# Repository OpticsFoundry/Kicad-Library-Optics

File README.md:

# KiCad Library for Optics

This repository includes a library for designing optical setups in KiCad.

Please visit our [website](https://www.opticsfoundry.com/) for more product and ordering.  
If you have any question or need help, write to us: opticsfoundry@gmail.com

## Table of Contents
- [Introduction](#introduction)
- [How to add library to KiCad](#how-to-add-library-to-kiCad)
- [Start a new design](#start-a-new-design)
  - [Schematic](#schematic)
  - [PCB](#pcb)
- [Free Projects](#free-projects)

---

## Introduction

[KiCad](https://www.kicad.org/) is an open source electronic design software. However, we have developed this library to be able to design optical setup.
The procedure of producing an optical setup with Robot developed by OpticsFoundry is shown below.

## How to add library to KiCad

1. Install KiCad from [here](https://www.kicad.org/),
2. Download or clone this repository to your computer as shown below,

3. Unzip the downloaded folder and move the folder to an appropriate path if you want,
4. Open the KiCad software, from `Preferences` tab, click on `Configure Paths...` as shown below,

5. Add a new path, name it `KIGITHUB` with path `https://github.com/KiCad`. As shown below,

6. Add another one and name it `KICAD_FIREFLY_OPTICS`, for the path click on folder icon and go to the path which the library has been downloaded then select `Optics` folder. As shown in following pictures,

7. At the end click on `OK` and close the window,
8. Now from `Preferences` tab, click on `Manage Symbol Libraries...`,
9. Add a new row and call it `Optics` with library path `${KICAD_FIREFLY_OPTICS}/Symbols/Optics.kicad_sym`. As shown below,

10. Then click on `OK` and close the window. If you encounter an error like below, probably the path is not defined correctly,

11. From `Preferences` tab, click on `Manage Footprint Libraries...`,
12. Add a new row and call it `Optics` with library path `${KICAD_FIREFLY_OPTICS}/Footprints/Optics.pretty`, at the end click on `OK` and close the window. As shown below,

13. To make sure the library has been added correctly, click on `Symbol Editor` and `Footprint Editor` in `Tools` tab. As shown below,

14. Search for `Optics` library in search bar, you should be able to see list of all the optical symbols and footprint. As shown in following pictures,

15. Done! Now you are ready to start a new optical design.

## Start a new design

Now you can start a new project and open schematic editor to design your optical setup, as shown below.

You could also copy one of the [examples](https://github.com/opticsfoundry/Kicad-Library-Optics/tree/main/Examples/) or use one of the [Free Projects](#free-projects) for starting point.

`Note` Standard optics hight is 7.5 mm, if optics hight of your components is smaller or bigger, please write to us: opticsfoundry@gmail.com

`Note` If you need a specific baseplate size or any other components which are not available in `Symbols`, please write to us: opticsfoundry@gmail.com

### Schematic

Based on your design, you need to choose baseplate size for your board.

If your page size is smaller than baseplate, you can change it in the page settings from `File` tab for schematic and footprint editors.

Schematic editor looks like this after adding baseplate.

I have added two collimators and mirrors to design a fiber to fiber setup.

By selecting wire, you can draw the beam path.

Each component need to be defined by selecting the component and changing the value based on what is your need.

### PCB

After finishing your design, save all changes in schematic editor. NOw you could move to PCB editor and update your PCB from Schematic.

`Note` You could also update PCB design each time after adding any new components.

Click on `Update PCB from Schematic...` in PCB editor, then update PCB and close the window as shown below.

Now the PCB looks like this:

Each component need to be selected and reposition and rerotate based on reality.

This example is available in [test](https://github.com/opticsfoundry/Kicad-Library-Optics/tree/main/Examples/test/)

## Free Projects
1. [AQuRA](https://github.com/opticsfoundry/AQuRA-KiCad-Design-GitHub/)

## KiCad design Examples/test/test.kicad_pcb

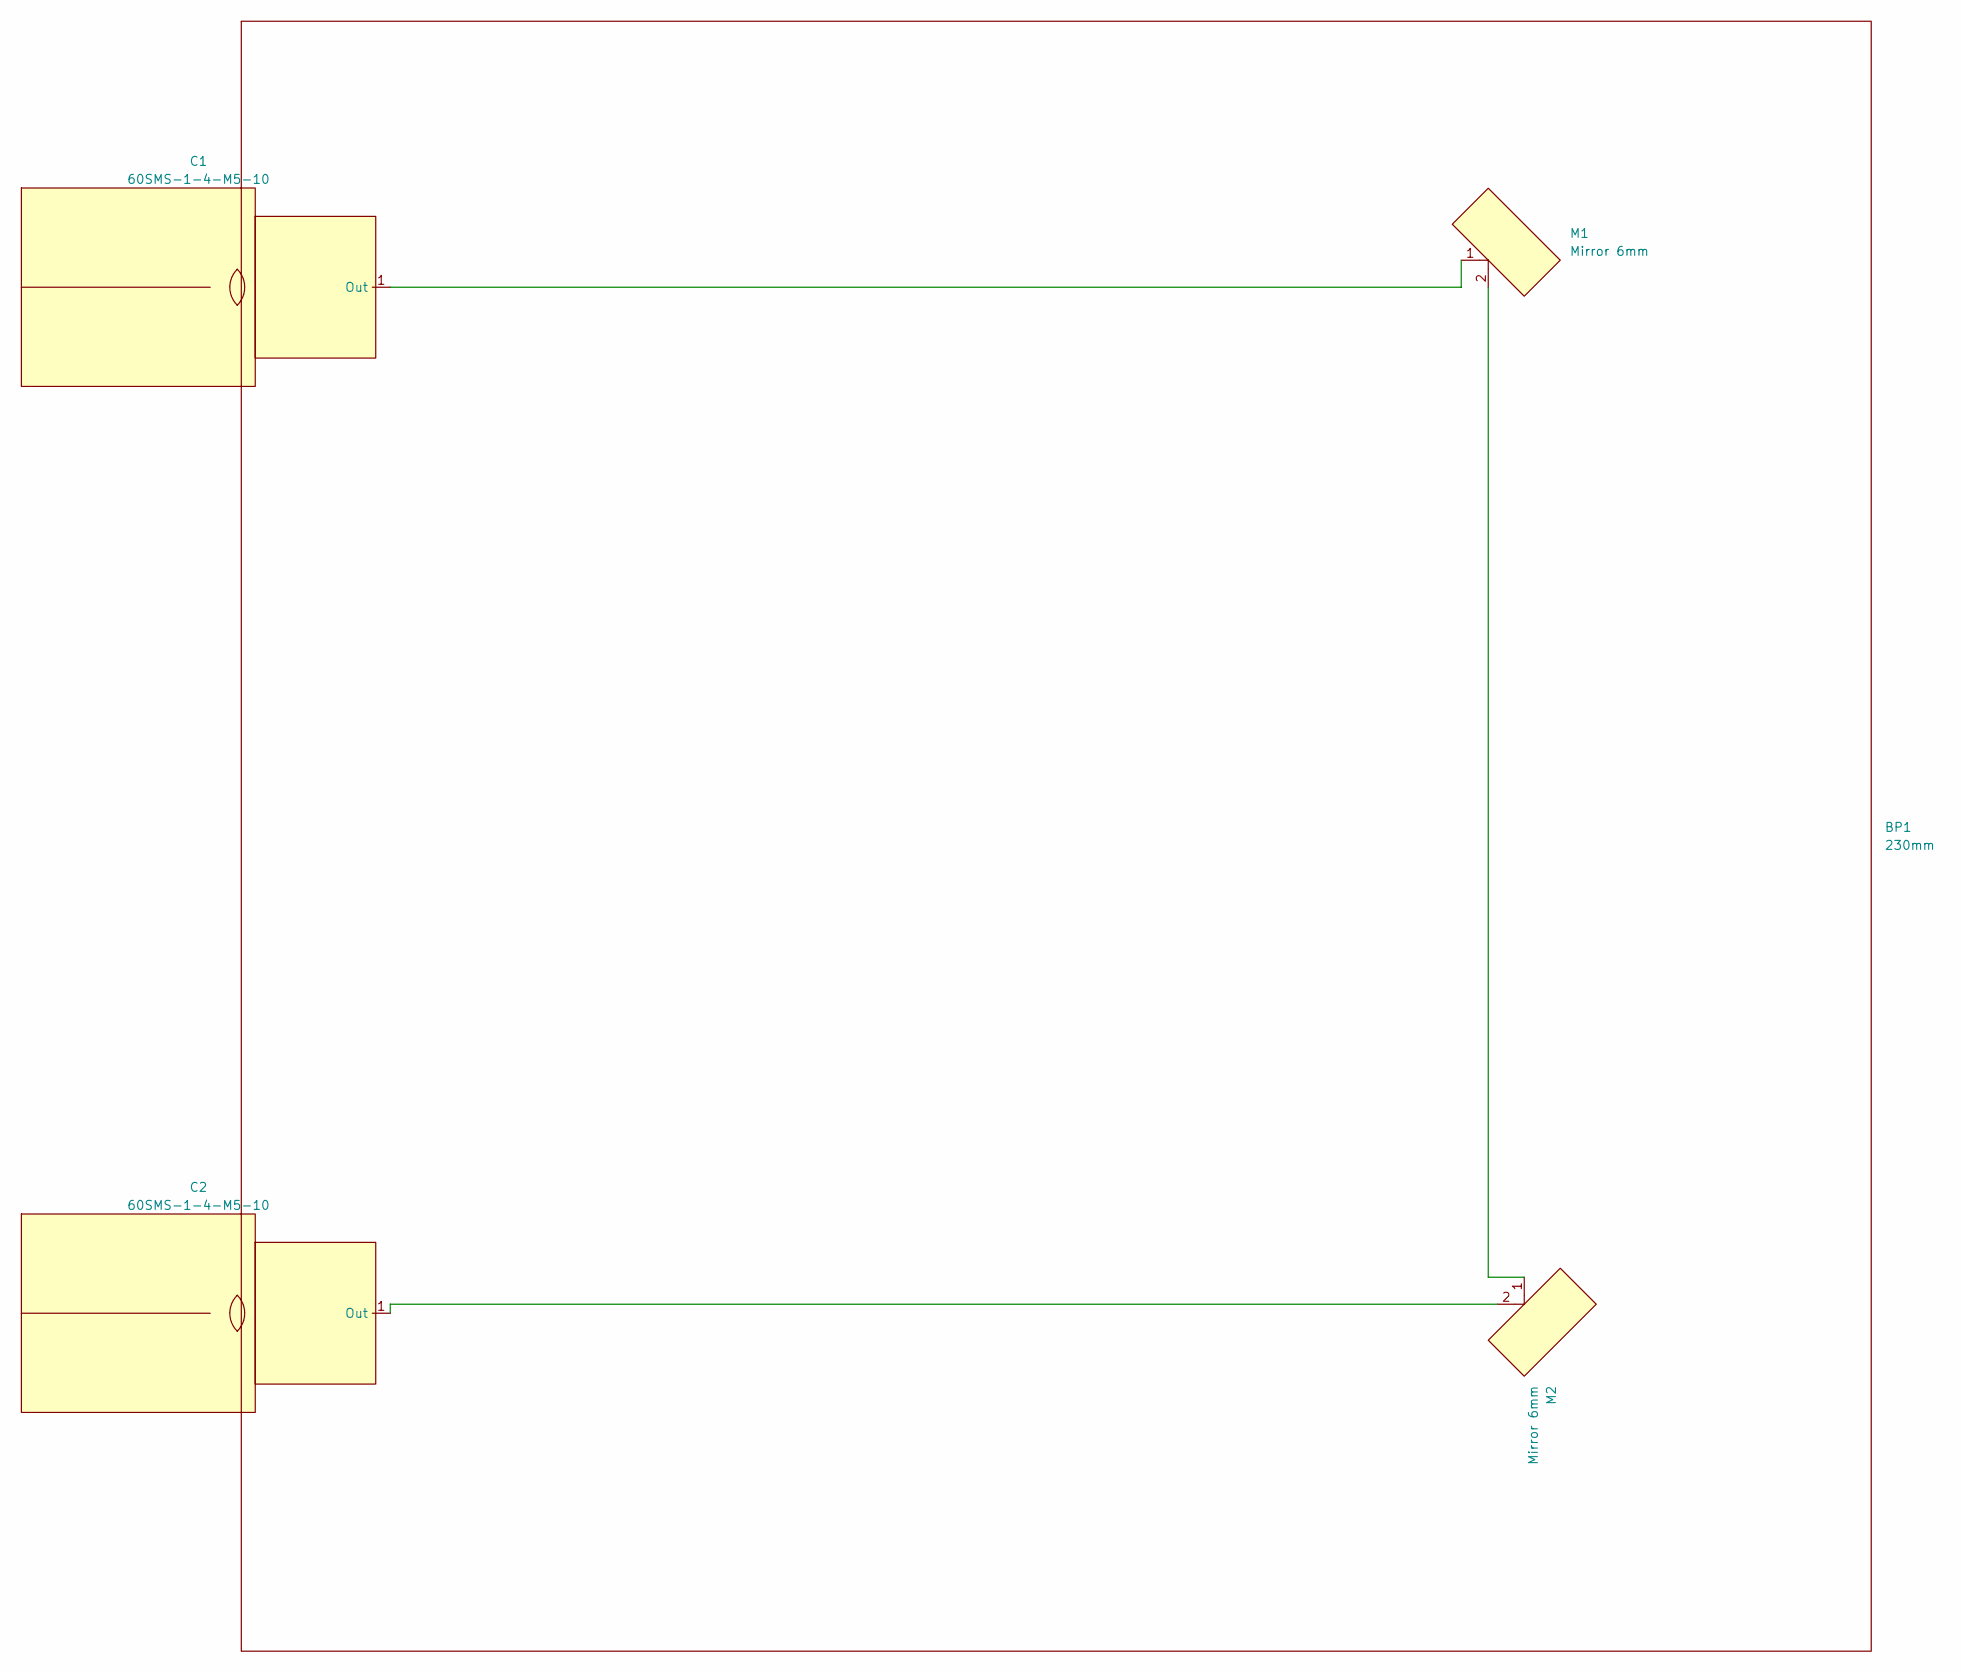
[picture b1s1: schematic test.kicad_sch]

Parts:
BP1: 230mm; Baseplate230mm
C1, C2: 60SMS-1-4-M5-10; S&KCollimator_V1
M1, M2: Mirror 6mm; Mirror6mm

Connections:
unnamed: C1.1 (Out), M1.1 (In)
unnamed: C2.1 (Out), M2.2 (Out)
unnamed: M1.2 (Out), M2.1 (In)

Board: 2 copper layers, 5 parts (0 on the bottom side), 3 nets, no tracks yet.

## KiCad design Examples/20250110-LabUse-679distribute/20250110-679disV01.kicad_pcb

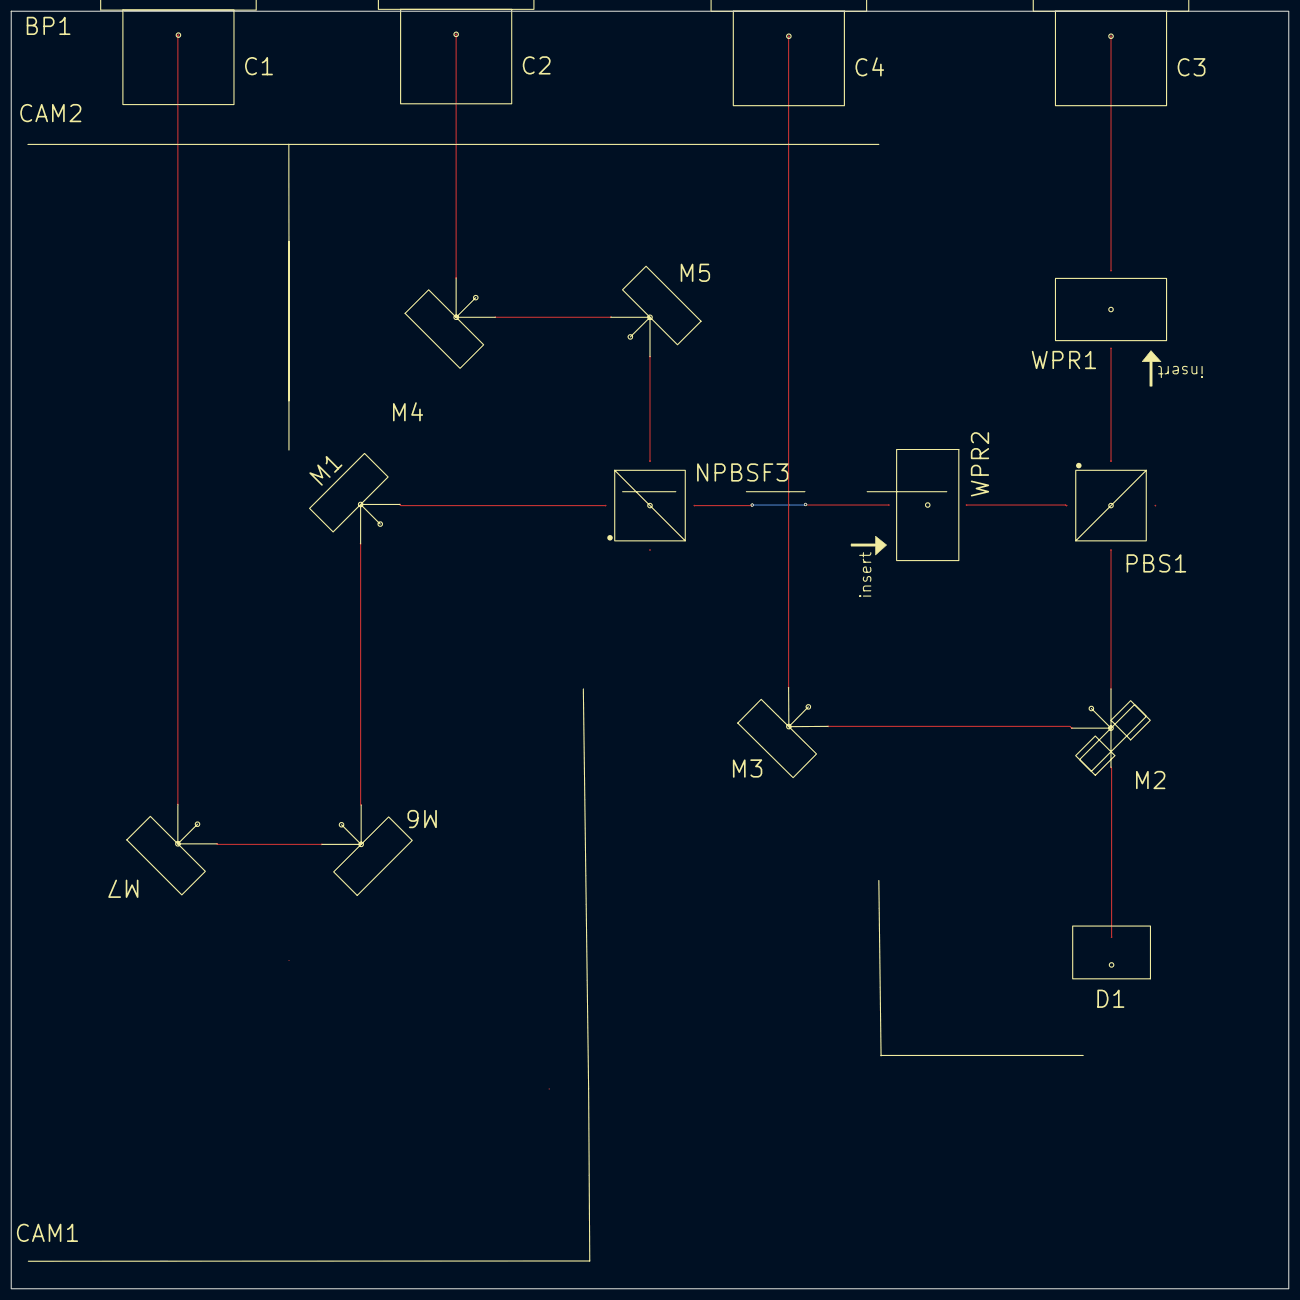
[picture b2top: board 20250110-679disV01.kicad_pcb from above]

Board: 2 copper layers, 230.0 x 230.0 mm, 17 parts (0 on the bottom side), 12 nets.

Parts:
BP1: 230mm; Baseplate230mm
C1: 689nm 9/2 Out, 60SMS-1-4-A4.5S-02; S&KCollimator_V1
C2, C4: 689nm 11/2 Out, 60SMS-1-4-A4.5S-02; S&KCollimator_V1
C3: 689nm Source, 60SMS-1-4-M5-10; S&KCollimator_V1
D1: Monitor; Detector
M1, M3, M4, M5, M6, M7: Mirror 6mm; Mirror6mm
M2: Mirror 3mm Polished; Mirror3mmRight
NPBSF3: NPBS-70:30-Flipped; PBS_Flipped
PBS1: PBSCasix689nm; PBS
WPR1, WPR2: L/2@689nm - Rotatable; WaveplateRotateable

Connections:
unnamed: C1.1 (Out), M7.2 (Out)
unnamed: C2.1 (Out), M4.2 (Out)
unnamed: C3.1 (Out), WPR1.1 (In)
unnamed: C4.1 (Out), M3.2 (Out)
unnamed: D1.1 (In), M2.3 (Leak)
unnamed: M1.1 (In), M6.1 (In)
unnamed: M2.1 (In), PBS1.2 (H)
unnamed: M2.2 (Out), M3.1 (In)
unnamed: M4.1 (In), M5.1 (In)
unnamed: M6.2 (Out), M7.1 (In)
unnamed: PBS1.1 (In), WPR1.2 (Out)
unnamed: PBS1.3 (V), WPR2.1 (In)

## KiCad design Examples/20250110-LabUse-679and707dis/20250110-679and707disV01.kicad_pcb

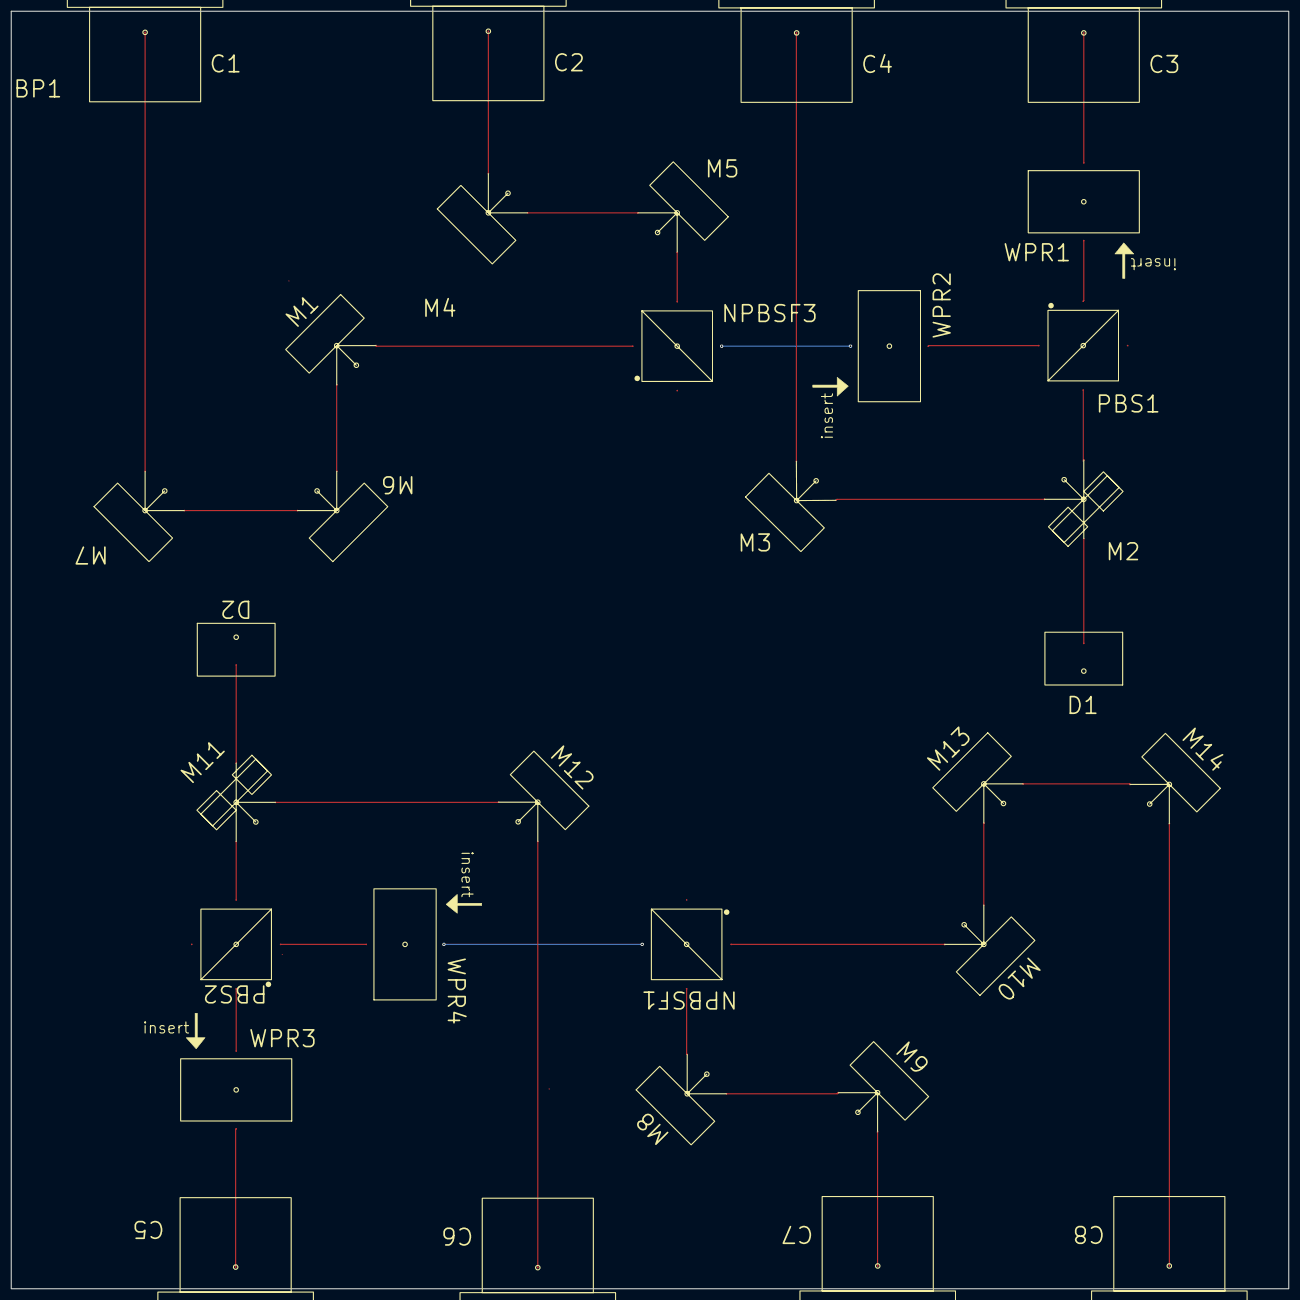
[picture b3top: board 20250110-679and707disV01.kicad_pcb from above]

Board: 2 copper layers, 230.0 x 230.0 mm, 33 parts (0 on the bottom side), 24 nets.

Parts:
BP1: 230mm; Baseplate230mm
C1, C8: 689nm 9/2 Out, 60SMS-1-4-A4.5S-02; S&KCollimator_V1
C2, C4, C6, C7: 689nm 11/2 Out, 60SMS-1-4-A4.5S-02; S&KCollimator_V1
C3, C5: 689nm Source, 60SMS-1-4-M5-10; S&KCollimator_V1
D1, D2: Monitor; Detector
M1, M3, M4, M5, M6, M7, M8, M9, M10, M12, M13, M14: Mirror 6mm; Mirror6mm
M2, M11: Mirror 3mm Polished; Mirror3mmRight
NPBSF1, NPBSF3: NPBS-70:30-Flipped; PBS_Flipped
PBS1, PBS2: PBSCasix689nm; PBS
WPR1, WPR2, WPR3, WPR4: L/2@689nm - Rotatable; WaveplateRotateable

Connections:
unnamed: C1.1 (Out), M7.2 (Out)
unnamed: C2.1 (Out), M4.2 (Out)
unnamed: C3.1 (Out), WPR1.1 (In)
unnamed: C4.1 (Out), M3.2 (Out)
unnamed: C5.1 (Out), WPR3.1 (In)
unnamed: C6.1 (Out), M12.2 (Out)
unnamed: C7.1 (Out), M9.2 (Out)
unnamed: C8.1 (Out), M14.2 (Out)
unnamed: D1.1 (In), M2.3 (Leak)
unnamed: D2.1 (In), M11.3 (Leak)
unnamed: M1.1 (In), M6.1 (In)
unnamed: M2.1 (In), PBS1.2 (H)
unnamed: M2.2 (Out), M3.1 (In)
unnamed: M4.1 (In), M5.1 (In)
unnamed: M6.2 (Out), M7.1 (In)
unnamed: M8.1 (In), M9.1 (In)
unnamed: M10.1 (In), M13.1 (In)
unnamed: M11.1 (In), PBS2.2 (H)
unnamed: M11.2 (Out), M12.1 (In)
unnamed: M13.2 (Out), M14.1 (In)
unnamed: PBS1.1 (In), WPR1.2 (Out)
unnamed: PBS1.3 (V), WPR2.1 (In)
unnamed: PBS2.1 (In), WPR3.2 (Out)
unnamed: PBS2.3 (V), WPR4.1 (In)

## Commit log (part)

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2025-02-19 add library for symbols and footprints.
2025-02-19 add rst file
2025-02-19 modify
2025-02-19 back to md format
2025-02-19 add image
2025-02-19 how to add library to kicad
2025-02-19 add examples
2025-02-19 add schematic
2025-02-19 add pcb part
2025-03-03 add new 280x230 mm baseplate
2025-10-04 Create LICENSE
